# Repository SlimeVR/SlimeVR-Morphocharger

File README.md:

# SlimeVR Morpho Charger
Charging dock for SlimeVR Butterfly trackers. Ten tracker stations and a dongle port behind four cascaded USB hubs, so trackers charge and stay reachable over USB.

## License
The hardware design in [`pcb/`](pcb) (schematics, PCB layout, symbol and footprint libraries) is licensed under the
CERN Open Hardware Licence Version 2 - Permissive ([LICENSE-CERN-OHL-P](LICENSE-CERN-OHL-P) or https://ohwr.org/cern_ohl_p_v2.txt).

Everything else, including the EEPROM tooling in [`eeprom/`](eeprom), is dual-licensed under either:

- MIT License ([LICENSE-MIT](LICENSE-MIT) or https://opensource.org/license/mit/)
- Apache License, Version 2.0 ([LICENSE-APACHE](LICENSE-APACHE) or https://opensource.org/license/apache-2-0/)

at your option.

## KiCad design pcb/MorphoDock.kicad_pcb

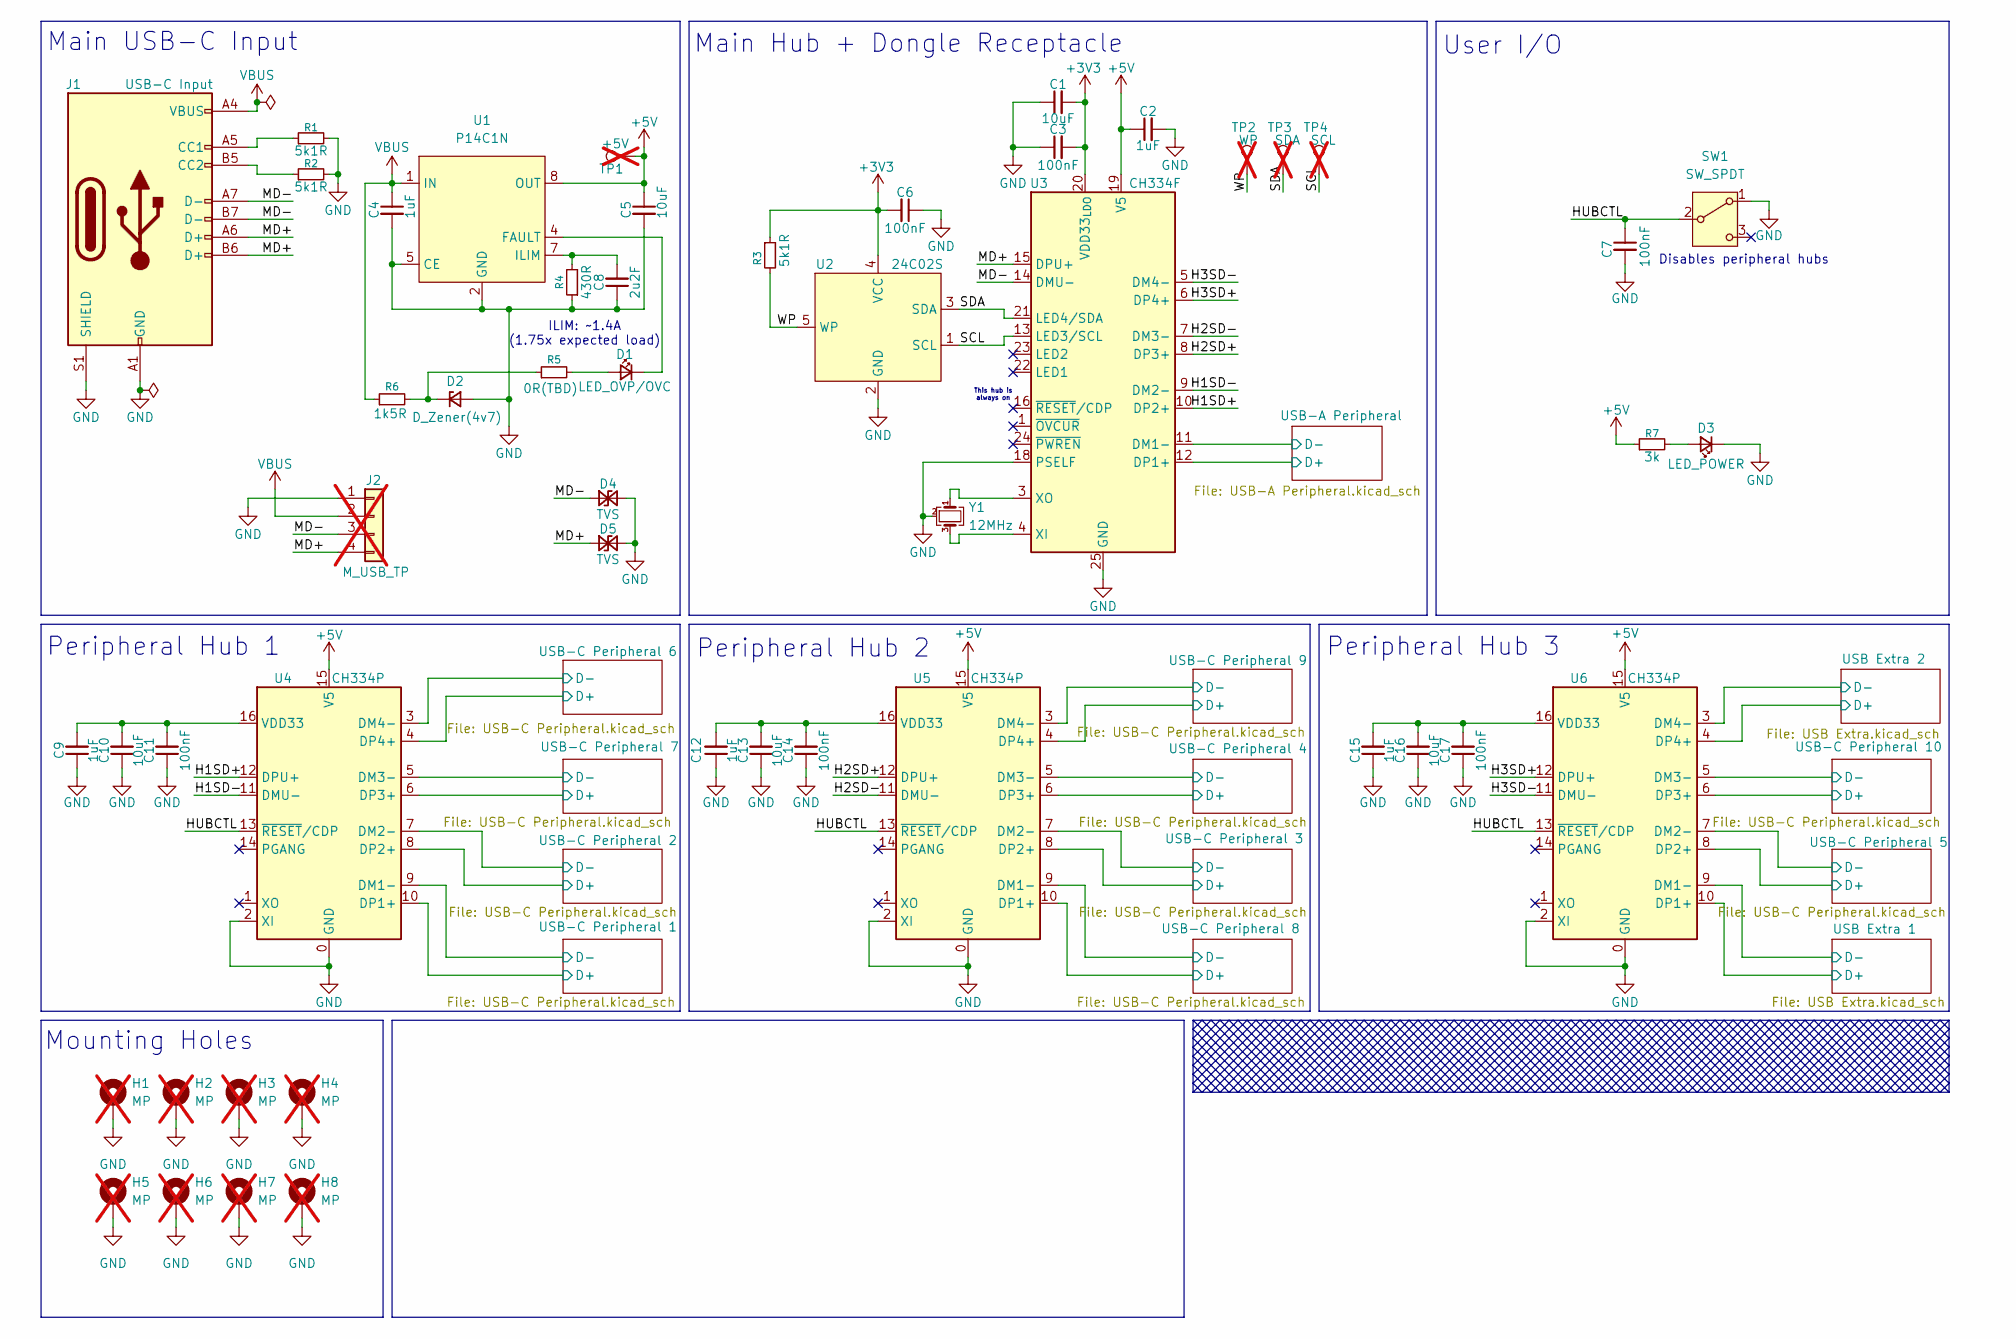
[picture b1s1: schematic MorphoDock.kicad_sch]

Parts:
C1, C5, C10, C13, C16: 10uF; C_0603; MPN C19702
C2, C4, C9, C12, C15: 1uF; C_0603; MPN C5199872
C3, C6, C7, C11, C14, C17: 100nF; C_0603; MPN C1591
C8: 2u2F; C_0603; MPN C86018
D1: LED_OVP/OVC; LED_SMD_1.7x0.6_H; MPN C125114
D2: D_Zener(4v7); D_SOD-123; MPN C173408
D3: LED_POWER; LED_SMD_1.7x0.6_H; MPN C125113
D4, D5: TVS; D_TVS_0603; MPN C10677
H1, H2, H3, H4, H5, H6, H7, H8: MP; MPN N/A; not fitted
J1: USB-C Input; USB-C_SMD_F_H; MPN C2765186
J2: M_USB_TP; TP_THT_2x2_2.54mm; MPN N/A; not fitted
R1, R2, R3: 5k1R; R_0603; MPN C23186
R4: 430R; R_0603; MPN C23170
R5: 0R(TBD); R_0603; MPN C21189
R6: 1k5R; R_1210; MPN C422399
R7: 3k; R_0603; MPN C4211
SW1: SW_SPDT; SW_THT_SK12D07VG4; MPN C393937
TP1: +5V; TP_THT_1x1_2.54mm; MPN N/A; not fitted
TP2: WP; TP_THT_1x1_2.54mm; MPN N/A; not fitted
TP3: SDA; TP_THT_1x1_2.54mm; MPN N/A; not fitted
TP4: SCL; TP_THT_1x1_2.54mm; MPN N/A; not fitted
U1: P14C1N; DFN-8_2x2_P0.5_EP0.8x1.6; MPN C1021678
U2: 24C02S; SOT-23-5; MPN C18723540
U3: CH334F; QFN-24-4x4-P0.5-EP2.7; MPN C5187527
U4, U5, U6: CH334P; QFN-16-3x3; MPN C5373042
Y1: 12MHz; XTAL_3225_4P; MPN C9002

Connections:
+3V3: C1.2, C3.2, C6.2, R3.1, U2.4 (VCC), U3.20 (VDD33_{LDO})
+5V: C2.1, C5.1, R7.1, TP1.1 (1_1), U1.8 (OUT), U3.19 (V5), U4.15 (V5), U5.15 (V5), U6.15 (V5); also elsewhere on the board
/H1SD+: U3.10 (DP2+), U4.12 (DPU+)
/H1SD-: U3.9 (DM2-), U4.11 (DMU-)
/H2SD+: U3.8 (DP3+), U5.12 (DPU+)
/H2SD-: U3.7 (DM3-), U5.11 (DMU-)
/H3SD+: U3.6 (DP4+), U6.12 (DPU+)
/H3SD-: U3.5 (DM4-), U6.11 (DMU-)
/HUBCTL: C7.1, SW1.2 (B), U4.13 (~RESET/CDP), U5.13 (~RESET/CDP), U6.13 (~RESET/CDP)
/MD+: D5.1 (A1), J1.A6 (D+), J1.B6 (D+), J2.4, U3.15 (DPU+)
/MD-: D4.1 (A1), J1.A7 (D-), J1.B7 (D-), J2.3, U3.14 (DMU-)
/SCL: TP4.1 (1_1), U2.1 (SCL), U3.13 (LED3/SCL)
/SDA: TP3.1 (1_1), U2.3 (SDA), U3.21 (LED4/SDA)
/USB Extra 1/D+: U6.10 (DP1+); also elsewhere on the board
/USB Extra 1/D-: U6.9 (DM1-); also elsewhere on the board
/USB Extra 2/D+: U6.4 (DP4+); also elsewhere on the board
/USB Extra 2/D-: U6.3 (DM4-); also elsewhere on the board
/USB-A Peripheral/D+: U3.12 (DP1+); also elsewhere on the board
/USB-A Peripheral/D-: U3.11 (DM1-); also elsewhere on the board
/USB-C Peripheral 1/D+: U4.10 (DP1+); also elsewhere on the board
/USB-C Peripheral 1/D-: U4.9 (DM1-); also elsewhere on the board
/USB-C Peripheral 2/D+: U4.8 (DP2+); also elsewhere on the board
/USB-C Peripheral 2/D-: U4.7 (DM2-); also elsewhere on the board
/USB-C Peripheral 3/D+: U5.8 (DP2+); also elsewhere on the board
/USB-C Peripheral 3/D-: U5.7 (DM2-); also elsewhere on the board
/USB-C Peripheral 4/D+: U5.6 (DP3+); also elsewhere on the board
/USB-C Peripheral 4/D-: U5.5 (DM3-); also elsewhere on the board
/USB-C Peripheral 5/D+: U6.8 (DP2+); also elsewhere on the board
/USB-C Peripheral 5/D-: U6.7 (DM2-); also elsewhere on the board
/USB-C Peripheral 6/D+: U4.4 (DP4+); also elsewhere on the board
/USB-C Peripheral 6/D-: U4.3 (DM4-); also elsewhere on the board
/USB-C Peripheral 7/D+: U4.6 (DP3+); also elsewhere on the board
/USB-C Peripheral 7/D-: U4.5 (DM3-); also elsewhere on the board
/USB-C Peripheral 8/D+: U5.10 (DP1+); also elsewhere on the board
/USB-C Peripheral 8/D-: U5.9 (DM1-); also elsewhere on the board
/USB-C Peripheral 9/D+: U5.4 (DP4+); also elsewhere on the board
/USB-C Peripheral 9/D-: U5.3 (DM4-); also elsewhere on the board
/USB-C Peripheral 10/D+: U6.6 (DP3+); also elsewhere on the board
/USB-C Peripheral 10/D-: U6.5 (DM3-); also elsewhere on the board
/WP: R3.2, TP2.1 (1_1), U2.5 (WP)
GND: C1.1, C2.2, C3.1, C4.2, C5.2, C6.1, C7.2, C8.1, C9.1, C10.1, C11.1, C12.1, C13.1, C14.1, C15.1, C16.1, C17.1, D2.2 (A), D3.1 (K), D4.2 (A2), D5.2 (A2), H1.1 (1_1), H2.1 (1_1), H3.1 (1_1), H4.1 (1_1), H5.1 (1_1), H6.1 (1_1), H7.1 (1_1), H8.1 (1_1), J1.A1 (GND), J1.A12 (GND), J1.B1 (GND), J1.B12 (GND), J1.S1 (SHIELD), J2.1, R1.2, R2.2, R4.1, SW1.1 (A), U1.2 (GND), U1.5 (CE), U2.2 (GND), U3.18 (PSELF), U3.25 (GND), U4.0 (GND), U4.2 (XI), U5.0 (GND), U5.2 (XI), U6.0 (GND), U6.2 (XI), Y1.2 (G), Y1.4 (G); also elsewhere on the board
unnamed: D1.2 (A), R5.2
unnamed: D1.1 (K), U1.4 (FAULT)
unnamed: D2.1 (K), R5.1, R6.2
unnamed: D3.2 (A), R7.2
unnamed: J1.A5 (CC1), R1.1
unnamed: J1.B5 (CC2), R2.1
unnamed: C8.2, R4.2, U1.7 (ILIM)
unnamed: U3.4 (XI), Y1.3
unnamed: U3.3 (XO), Y1.1
unnamed: C9.2, C10.2, C11.2, U4.16 (VDD33)
unnamed: C12.2, C13.2, C14.2, U5.16 (VDD33)
unnamed: C15.2, C16.2, C17.2, U6.16 (VDD33)
VBUS: C4.1, J1.A4 (VBUS), J1.A9 (VBUS), J1.B4 (VBUS), J1.B9 (VBUS), J2.2, R6.1, U1.1 (IN)

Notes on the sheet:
Disables peripheral hubs
Peripheral Hub 2
ILIM: ~1.4A (1.75x expected load)
User I/O
Peripheral Hub 3
This hub is always on
Peripheral Hub 1
Mounting Holes
Main Hub + Dongle Receptacle
Main USB-C Input

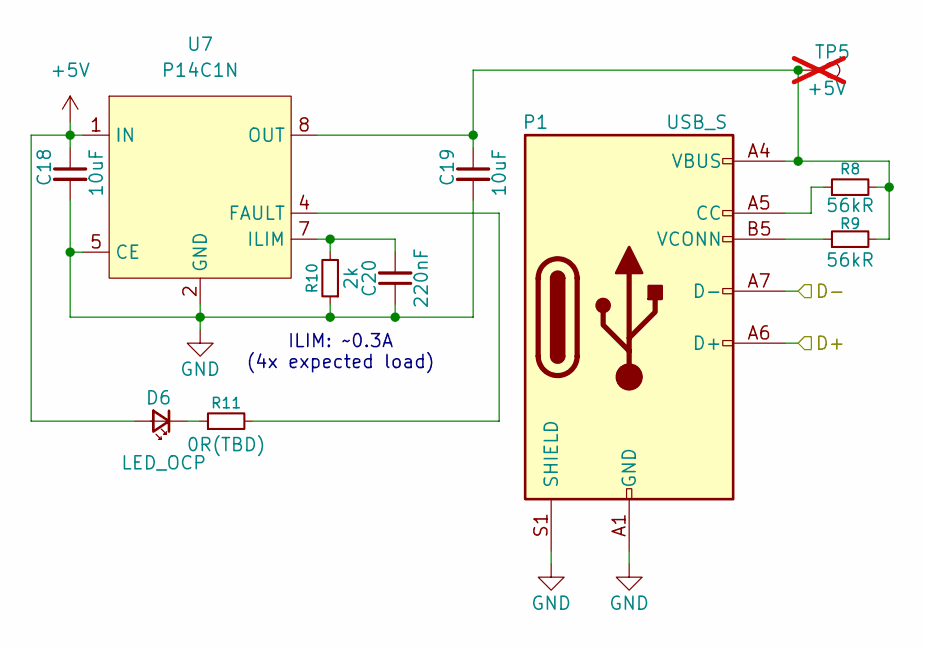
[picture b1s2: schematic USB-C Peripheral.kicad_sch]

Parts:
C18, C19: 10uF; C_0603; MPN C19702
C20: 220nF; C_0603; MPN C97857
D6: LED_OCP; LED_0603; MPN C125099
P1: USB_S; USB-C_H_M_V; MPN C6332285
R8, R9: 56kR; R_0603; MPN C23206
R10: 2k; R_0603; MPN C22975
R11: 0R(TBD); R_0603; MPN C21189
TP5: +5V; TP_THT_1x1_2.54mm; MPN N/A; not fitted
U7: P14C1N; DFN-8_2x2_P0.5_EP0.8x1.6; MPN C1021678

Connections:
+5V: C18.1, D6.2 (A), U7.1 (IN); also elsewhere on the board
/USB-C Peripheral 1/D+: P1.A6 (D+); also elsewhere on the board
/USB-C Peripheral 1/D-: P1.A7 (D-); also elsewhere on the board
GND: C18.2, C19.2, C20.1, P1.A1 (GND), P1.A12 (GND), P1.B1 (GND), P1.B12 (GND), P1.S1 (SHIELD), R10.1, U7.2 (GND), U7.5 (CE); also elsewhere on the board
unnamed: D6.1 (K), R11.1
unnamed: P1.A5 (CC), R8.1
unnamed: P1.B5 (VCONN), R9.1
unnamed: R11.2, U7.4 (FAULT)
unnamed: C20.2, R10.2, U7.7 (ILIM)
unnamed: C19.1, P1.A4 (VBUS), P1.A9 (VBUS), P1.B4 (VBUS), P1.B9 (VBUS), R8.2, R9.2, TP5.1 (1_1), U7.8 (OUT)

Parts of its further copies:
C21, C22, C24, C25, C27, C28, C30, C31, C33, C34, C36, C37, C39, C40, C42, C43, C45, C46: 10uF; C_0603; MPN C19702
C23, C26, C29, C32, C35, C38, C41, C44, C47: 220nF; C_0603; MPN C97857
D7, D8, D9, D10, D11, D12, D13, D14, D15: LED_OCP; LED_0603; MPN C125099
P2, P3, P4, P5, P6, P7, P8, P9, P10: USB_S; USB-C_H_M_V; MPN C6332285
R12, R13, R16, R17, R20, R21, R24, R25, R28, R29, R32, R33, R36, R37, R40, R41, R44, R45: 56kR; R_0603; MPN C23206
R14, R18, R22, R26, R30, R34, R38, R42, R46: 2k; R_0603; MPN C22975
R15, R19, R23, R27, R31, R35, R39, R43, R47: 0R(TBD); R_0603; MPN C21189
TP6, TP7, TP8, TP9, TP10, TP11, TP12, TP13, TP14: +5V; TP_THT_1x1_2.54mm; MPN N/A; not fitted
U8, U9, U10, U11, U12, U13, U14, U15, U16: P14C1N; DFN-8_2x2_P0.5_EP0.8x1.6; MPN C1021678

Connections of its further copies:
+5V: C21.1, C24.1, C27.1, C30.1, C33.1, C36.1, C39.1, C42.1, C45.1, D7.2 (A), D8.2 (A), D9.2 (A), D10.2 (A), D11.2 (A), D12.2 (A), D13.2 (A), D14.2 (A), D15.2 (A), U8.1 (IN), U9.1 (IN), U10.1 (IN), U11.1 (IN), U12.1 (IN), U13.1 (IN), U14.1 (IN), U15.1 (IN), U16.1 (IN); also elsewhere on the board
/USB-C Peripheral 2/D+: P2.A6 (D+); also elsewhere on the board
/USB-C Peripheral 2/D-: P2.A7 (D-); also elsewhere on the board
/USB-C Peripheral 3/D+: P3.A6 (D+); also elsewhere on the board
/USB-C Peripheral 3/D-: P3.A7 (D-); also elsewhere on the board
/USB-C Peripheral 4/D+: P4.A6 (D+); also elsewhere on the board
/USB-C Peripheral 4/D-: P4.A7 (D-); also elsewhere on the board
/USB-C Peripheral 5/D+: P5.A6 (D+); also elsewhere on the board
/USB-C Peripheral 5/D-: P5.A7 (D-); also elsewhere on the board
/USB-C Peripheral 6/D+: P6.A6 (D+); also elsewhere on the board
/USB-C Peripheral 6/D-: P6.A7 (D-); also elsewhere on the board
/USB-C Peripheral 7/D+: P7.A6 (D+); also elsewhere on the board
/USB-C Peripheral 7/D-: P7.A7 (D-); also elsewhere on the board
/USB-C Peripheral 8/D+: P8.A6 (D+); also elsewhere on the board
/USB-C Peripheral 8/D-: P8.A7 (D-); also elsewhere on the board
/USB-C Peripheral 9/D+: P9.A6 (D+); also elsewhere on the board
/USB-C Peripheral 9/D-: P9.A7 (D-); also elsewhere on the board
/USB-C Peripheral 10/D+: P10.A6 (D+); also elsewhere on the board
/USB-C Peripheral 10/D-: P10.A7 (D-); also elsewhere on the board
GND: C21.2, C22.2, C23.1, C24.2, C25.2, C26.1, C27.2, C28.2, C29.1, C30.2, C31.2, C32.1, C33.2, C34.2, C35.1, C36.2, C37.2, C38.1, C39.2, C40.2, C41.1, C42.2, C43.2, C44.1, C45.2, C46.2, C47.1, P2.A1 (GND), P2.A12 (GND), P2.B1 (GND), P2.B12 (GND), P2.S1 (SHIELD), P3.A1 (GND), P3.A12 (GND), P3.B1 (GND), P3.B12 (GND), P3.S1 (SHIELD), P4.A1 (GND), P4.A12 (GND), P4.B1 (GND), P4.B12 (GND), P4.S1 (SHIELD), P5.A1 (GND), P5.A12 (GND), P5.B1 (GND), P5.B12 (GND), P5.S1 (SHIELD), P6.A1 (GND), P6.A12 (GND), P6.B1 (GND), P6.B12 (GND), P6.S1 (SHIELD), P7.A1 (GND), P7.A12 (GND), P7.B1 (GND), P7.B12 (GND), P7.S1 (SHIELD), P8.A1 (GND), P8.A12 (GND), P8.B1 (GND), P8.B12 (GND), P8.S1 (SHIELD), P9.A1 (GND), P9.A12 (GND), P9.B1 (GND), P9.B12 (GND), P9.S1 (SHIELD), P10.A1 (GND), P10.A12 (GND), P10.B1 (GND), P10.B12 (GND), P10.S1 (SHIELD), R14.1, R18.1, R22.1, R26.1, R30.1, R34.1, R38.1, R42.1, R46.1, U8.2 (GND), U8.5 (CE), U9.2 (GND), U9.5 (CE), U10.2 (GND), U10.5 (CE), U11.2 (GND), U11.5 (CE), U12.2 (GND), U12.5 (CE), U13.2 (GND), U13.5 (CE), U14.2 (GND), U14.5 (CE), U15.2 (GND), U15.5 (CE), U16.2 (GND), U16.5 (CE); also elsewhere on the board
unnamed: D7.1 (K), R15.1
unnamed: D8.1 (K), R19.1
unnamed: D9.1 (K), R23.1
unnamed: D10.1 (K), R27.1
unnamed: D11.1 (K), R31.1
unnamed: D12.1 (K), R35.1
unnamed: D13.1 (K), R39.1
unnamed: D14.1 (K), R43.1
unnamed: D15.1 (K), R47.1
unnamed: P2.A5 (CC), R12.1
unnamed: P2.B5 (VCONN), R13.1
unnamed: P3.A5 (CC), R16.1
unnamed: P3.B5 (VCONN), R17.1
unnamed: P4.A5 (CC), R20.1
unnamed: P4.B5 (VCONN), R21.1
unnamed: P5.A5 (CC), R24.1
unnamed: P5.B5 (VCONN), R25.1
unnamed: P6.A5 (CC), R28.1
unnamed: P6.B5 (VCONN), R29.1
unnamed: P7.A5 (CC), R32.1
unnamed: P7.B5 (VCONN), R33.1
unnamed: P8.A5 (CC), R36.1
unnamed: P8.B5 (VCONN), R37.1
unnamed: P9.A5 (CC), R40.1
unnamed: P9.B5 (VCONN), R41.1
unnamed: P10.A5 (CC), R44.1
unnamed: P10.B5 (VCONN), R45.1
unnamed: R15.2, U8.4 (FAULT)
unnamed: C23.2, R14.2, U8.7 (ILIM)
unnamed: C22.1, P2.A4 (VBUS), P2.A9 (VBUS), P2.B4 (VBUS), P2.B9 (VBUS), R12.2, R13.2, TP6.1 (1_1), U8.8 (OUT)
unnamed: R19.2, U9.4 (FAULT)
unnamed: C26.2, R18.2, U9.7 (ILIM)
unnamed: C25.1, P3.A4 (VBUS), P3.A9 (VBUS), P3.B4 (VBUS), P3.B9 (VBUS), R16.2, R17.2, TP7.1 (1_1), U9.8 (OUT)
unnamed: R23.2, U10.4 (FAULT)
unnamed: C29.2, R22.2, U10.7 (ILIM)
unnamed: C28.1, P4.A4 (VBUS), P4.A9 (VBUS), P4.B4 (VBUS), P4.B9 (VBUS), R20.2, R21.2, TP8.1 (1_1), U10.8 (OUT)
unnamed: R27.2, U11.4 (FAULT)
unnamed: C32.2, R26.2, U11.7 (ILIM)
unnamed: C31.1, P5.A4 (VBUS), P5.A9 (VBUS), P5.B4 (VBUS), P5.B9 (VBUS), R24.2, R25.2, TP9.1 (1_1), U11.8 (OUT)
unnamed: R31.2, U12.4 (FAULT)
unnamed: C35.2, R30.2, U12.7 (ILIM)
unnamed: C34.1, P6.A4 (VBUS), P6.A9 (VBUS), P6.B4 (VBUS), P6.B9 (VBUS), R28.2, R29.2, TP10.1 (1_1), U12.8 (OUT)
unnamed: R35.2, U13.4 (FAULT)
unnamed: C38.2, R34.2, U13.7 (ILIM)
unnamed: C37.1, P7.A4 (VBUS), P7.A9 (VBUS), P7.B4 (VBUS), P7.B9 (VBUS), R32.2, R33.2, TP11.1 (1_1), U13.8 (OUT)
unnamed: R39.2, U14.4 (FAULT)
unnamed: C41.2, R38.2, U14.7 (ILIM)
unnamed: C40.1, P8.A4 (VBUS), P8.A9 (VBUS), P8.B4 (VBUS), P8.B9 (VBUS), R36.2, R37.2, TP12.1 (1_1), U14.8 (OUT)
unnamed: R43.2, U15.4 (FAULT)
unnamed: C44.2, R42.2, U15.7 (ILIM)
unnamed: C43.1, P9.A4 (VBUS), P9.A9 (VBUS), P9.B4 (VBUS), P9.B9 (VBUS), R40.2, R41.2, TP13.1 (1_1), U15.8 (OUT)
unnamed: R47.2, U16.4 (FAULT)
unnamed: C47.2, R46.2, U16.7 (ILIM)
unnamed: C46.1, P10.A4 (VBUS), P10.A9 (VBUS), P10.B4 (VBUS), P10.B9 (VBUS), R44.2, R45.2, TP14.1 (1_1), U16.8 (OUT)

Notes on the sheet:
ILIM: ~0.3A (4x expected load)

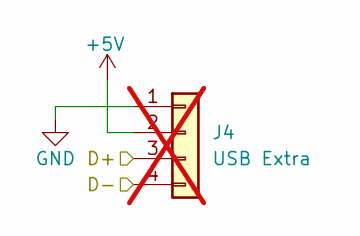
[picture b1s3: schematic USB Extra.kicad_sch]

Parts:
J4: USB Extra; TP_THT_2x2_2.54mm; not fitted

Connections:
+5V: J4.2; also elsewhere on the board
/USB Extra 1/D+: J4.3; also elsewhere on the board
/USB Extra 1/D-: J4.4; also elsewhere on the board
GND: J4.1; also elsewhere on the board

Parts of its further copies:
J5: USB Extra; TP_THT_2x2_2.54mm; not fitted

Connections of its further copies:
+5V: J5.2; also elsewhere on the board
/USB Extra 2/D+: J5.3; also elsewhere on the board
/USB Extra 2/D-: J5.4; also elsewhere on the board
GND: J5.1; also elsewhere on the board

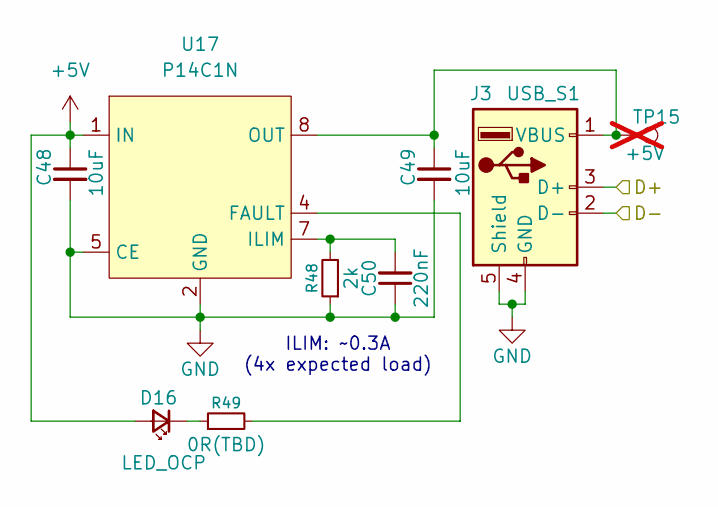
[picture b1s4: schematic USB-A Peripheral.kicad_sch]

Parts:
C48, C49: 10uF; C_0603; MPN C19702
C50: 220nF; C_0603; MPN C97857
D16: LED_OCP; LED_0603; MPN C125099
J3: USB_S1; USB-A_THT_F_V; MPN C42543
R48: 2k; R_0603; MPN C22975
R49: 0R(TBD); R_0603; MPN C21189
TP15: +5V; TP_THT_1x1_2.54mm; MPN N/A; not fitted
U17: P14C1N; DFN-8_2x2_P0.5_EP0.8x1.6; MPN C1021678

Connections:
+5V: C48.1, D16.2 (A), U17.1 (IN); also elsewhere on the board
/USB-A Peripheral/D+: J3.3 (D+); also elsewhere on the board
/USB-A Peripheral/D-: J3.2 (D-); also elsewhere on the board
GND: C48.2, C49.2, C50.1, J3.4 (GND), J3.5 (Shield), R48.1, U17.2 (GND), U17.5 (CE); also elsewhere on the board
unnamed: D16.1 (K), R49.1
unnamed: C49.1, J3.1 (VBUS), TP15.1 (1_1), U17.8 (OUT)
unnamed: R49.2, U17.4 (FAULT)
unnamed: C50.2, R48.2, U17.7 (ILIM)

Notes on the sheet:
ILIM: ~0.3A (4x expected load)

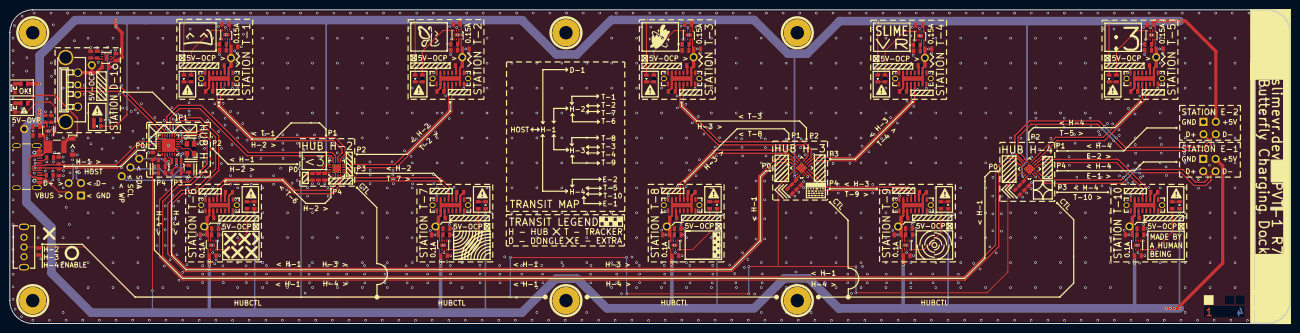
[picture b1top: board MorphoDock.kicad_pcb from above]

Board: 4 copper layers, 262.9 x 64.4 mm, 172 parts (0 on the bottom side), 118 nets.
